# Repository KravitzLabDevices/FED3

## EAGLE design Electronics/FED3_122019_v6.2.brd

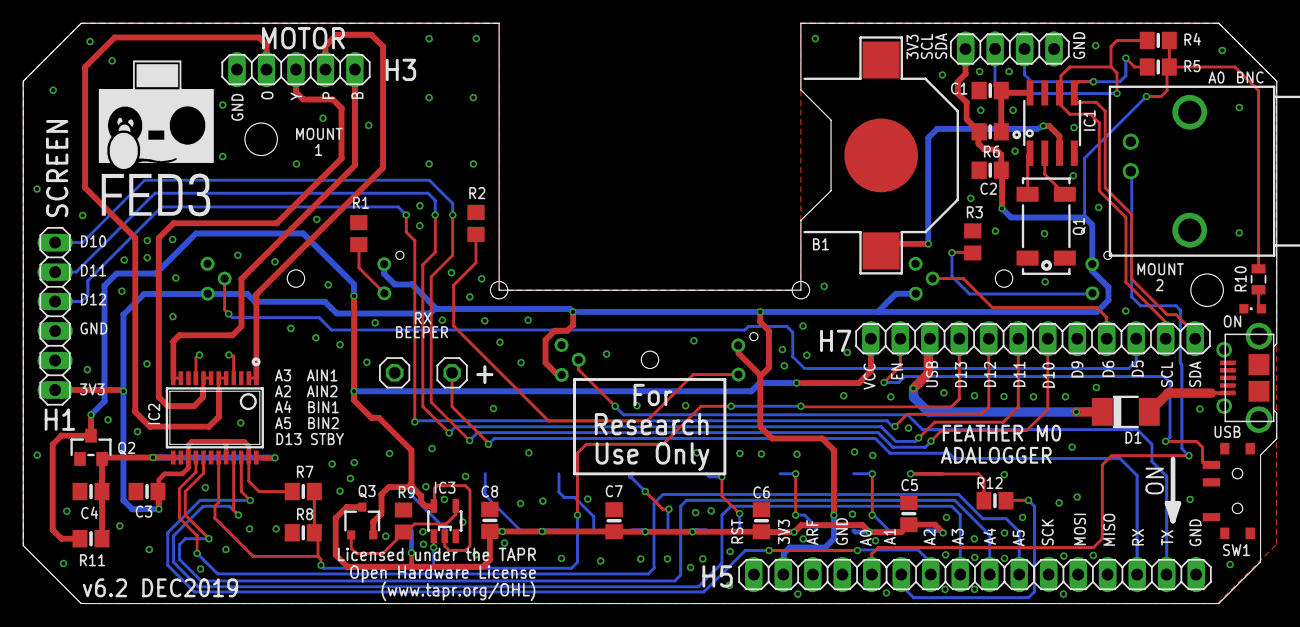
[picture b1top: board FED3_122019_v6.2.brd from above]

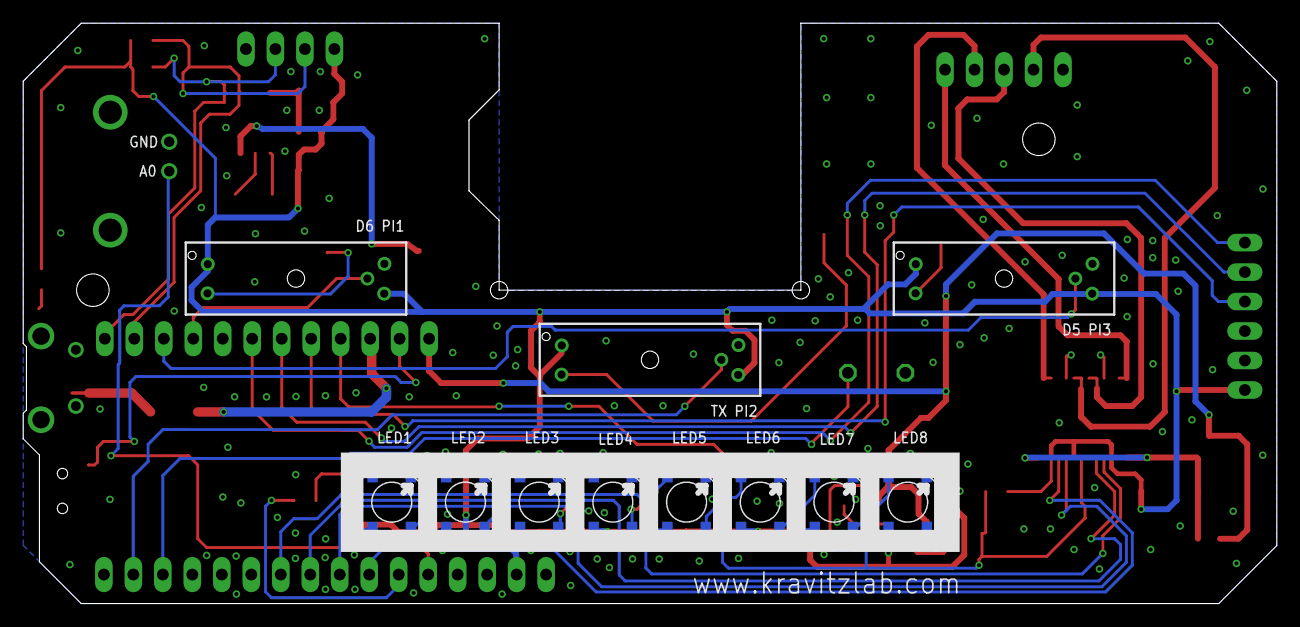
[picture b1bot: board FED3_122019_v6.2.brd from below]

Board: 2 copper layers, 108.0 x 50.0 mm, 50 parts (11 on the bottom side), 45 nets.

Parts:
AUX_I2C: 1X04
B1: CR1220
BEEP1, BEEP2: 1X01
BNC: BNC; BNC_RA
C1, C2, C5, C6, C7, C8: 10uF; 0805-NO
C3, C4: 10µF; 0805-NO
D1: DO-214AC
FEATHER_L: 1X16
FEATHER_R: 1X12
IC1: RTC_PCF8523T; SOIC8_150MIL
IC2: TB6612 SSOP; SSOP24
IC3: M74VHC1GT50DTT1G; SOT23-5
LED1, LED2, LED3, LED4, LED5, LED6, LED7, LED8: WS2812B5050; WS2812B
MOTOR: 1X05
ON: CHIPLED_0603
PI1, PI2, PI3: GP1A57HR
Q1: 32.768; CRYSTAL_8X3.8
Q2: DMG3415; SOT23-WIDE
Q3: TSMT3
R1, R2, R3: 1k; R0805
R4, R5: 4K7; 0805-NO
R6: 1K; 0805-NO
R7: DNI; 0805-NO
R8: 4k7; 0805-NO
R9: 37k; R0805
R10: 1k3; 0805
R11: 0; 0805-NO
R12: 470; 0805-NO
SCREEN: 1X06
SW1: SSSS811101
USB: USB_MICRO_B; ZX62D-B-5P8

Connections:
3V3: AUX_I2C.1, C2.1, C3.1, FEATHER_L.2, IC2.15, IC2.20, IC2.23, PI1.1, PI1.3, PI2.1, PI2.3, PI3.1, PI3.3, R4.1, R5.2, R6.1, R7.2, R10.2, SCREEN.6
A0: BNC.1, FEATHER_L.5
A1: FEATHER_L.6, R12.2
A2: FEATHER_L.7, IC2.22
A3: FEATHER_L.8, IC2.21
A4: FEATHER_L.9, IC2.17
A5: FEATHER_L.10, IC2.16
BLUE: IC2.11, IC2.12, MOTOR.5
D5: FEATHER_R.10, PI3.4
D6: FEATHER_R.9, PI1.4
D10: FEATHER_R.7, SCREEN.1
D11: FEATHER_R.6, SCREEN.2
D12: FEATHER_R.5, SCREEN.3
D13: FEATHER_R.4, IC2.19, IC3.1, R7.1, R8.2
EN: FEATHER_R.2, SW1.3
GND: AUX_I2C.4, B1.-, BEEP2.1, BNC.2, C1.2, C2.2, C3.2, C4.2, C5.2, C6.2, C7.2, C8.2, FEATHER_L.4, FEATHER_L.16, IC1.4, IC2.3, IC2.4, IC2.9, IC2.10, IC2.18, IC3.3, LED1.3-GND, LED2.3-GND, LED3.3-GND, LED4.3-GND, LED5.3-GND, LED6.3-GND, LED7.3-GND, LED8.3-GND, MOTOR.1, ON.C, PI1.5, PI2.5, PI3.5, Q2.1, R1.2, R2.2, R3.2, R8.1, R9.1, SCREEN.4, SW1.2, USB.P$5
unnamed: PI2.2, R2.1
unnamed: PI3.2, R1.1
unnamed: PI1.2, R3.1
unnamed: D1.A, USB.P$1
unnamed: LED1.2-DOUT, LED2.4-DIN
unnamed: C1.1, IC1.8, R6.2
unnamed: LED2.2-DOUT, LED3.4-DIN
unnamed: ON.A, R10.1
unnamed: LED3.2-DOUT, LED4.4-DIN
unnamed: LED4.2-DOUT, LED5.4-DIN
unnamed: LED5.2-DOUT, LED6.4-DIN
unnamed: LED6.2-DOUT, LED7.4-DIN
unnamed: LED7.2-DOUT, LED8.4-DIN
unnamed: IC1.1, Q1.P$1
unnamed: IC1.2, Q1.P$4
unnamed: LED1.4-DIN, R12.1
ORANGE: IC2.5, IC2.6, MOTOR.2
OUT3: IC3.4, Q3.P$1, R9.2
PINK: IC2.1, IC2.2, MOTOR.4
RX: BEEP1.1, FEATHER_L.14
SCL: AUX_I2C.2, FEATHER_R.11, IC1.6, R4.2
SDA: AUX_I2C.3, FEATHER_R.12, IC1.5, R5.1
TX: FEATHER_L.15, PI2.4
USB: D1.C, FEATHER_R.3
VBAT1: B1.+$1, IC1.3
VCC: FEATHER_R.1, IC3.2, IC3.5, Q2.3, Q3.P$2, R11.2
VCCNEO: C5.1, C6.1, C7.1, C8.1, LED1.1-VDD, LED2.1-VDD, LED3.1-VDD, LED4.1-VDD, LED5.1-VDD, LED6.1-VDD, LED7.1-VDD, LED8.1-VDD, Q3.P$3
VMOTOR: C4.1, IC2.13, IC2.14, IC2.24, Q2.2, R11.1
YELLOW: IC2.7, IC2.8, MOTOR.3

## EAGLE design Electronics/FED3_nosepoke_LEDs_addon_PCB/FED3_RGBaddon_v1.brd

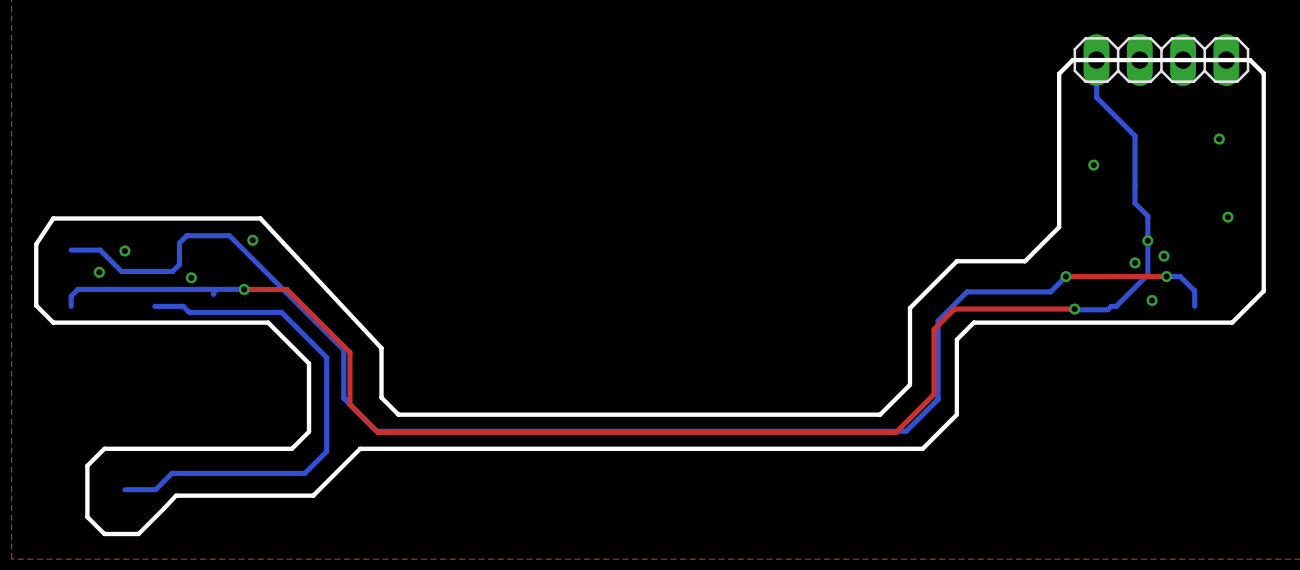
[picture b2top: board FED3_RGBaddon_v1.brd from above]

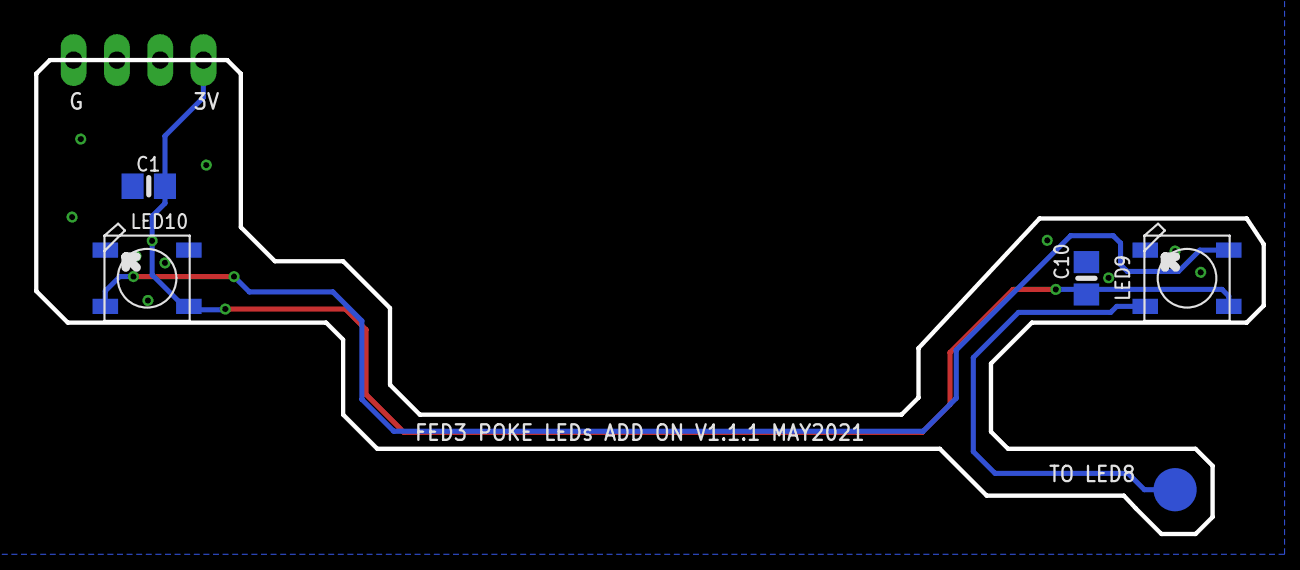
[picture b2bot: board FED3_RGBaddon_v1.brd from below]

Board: 2 copper layers, 72.0 x 27.8 mm, 6 parts (5 on the bottom side), 4 nets.

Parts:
AUX_I2C: 1X04
C1, C10: 10uF; 0805-NO
LED9, LED10: WS2812B5050; WS2812B
NEOINPUT: PTR1B2,54; B2,54

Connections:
3V3: AUX_I2C.1, C1.1, C10.1, LED9.1-VDD, LED10.1-VDD
A1: LED9.4-DIN, NEOINPUT.TP
GND: AUX_I2C.4, C1.2, C10.2, LED9.3-GND, LED10.3-GND
unnamed: LED9.2-DOUT, LED10.4-DIN

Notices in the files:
Electronics/FED3_122019_v6.2.brd:
Licensed under the TAPR
Open Hardware License
Licensed under the TAPR Open
Hardware License (www.tapr.org/OHL)
Copyright 2019 Mohamed Ali, FIlipe Carvalho, Alexxai Kravitz
parts and their libraries:
microbuilder: This work is placed in the public domain, and may be freely used for commercial and non-commercial work with the following conditions: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
